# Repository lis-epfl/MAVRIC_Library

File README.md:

# MAV'RIC Library
Open source library for MAV'RIC autopilots

For information about the installation and usage, have a look at the [Online Documentation](http://lis-epfl.github.io/MAVRIC_Library/) and the [Doxygen Documentation](http://lis-epfl.github.io/MAVRIC_Library/doxygen/classes.html)

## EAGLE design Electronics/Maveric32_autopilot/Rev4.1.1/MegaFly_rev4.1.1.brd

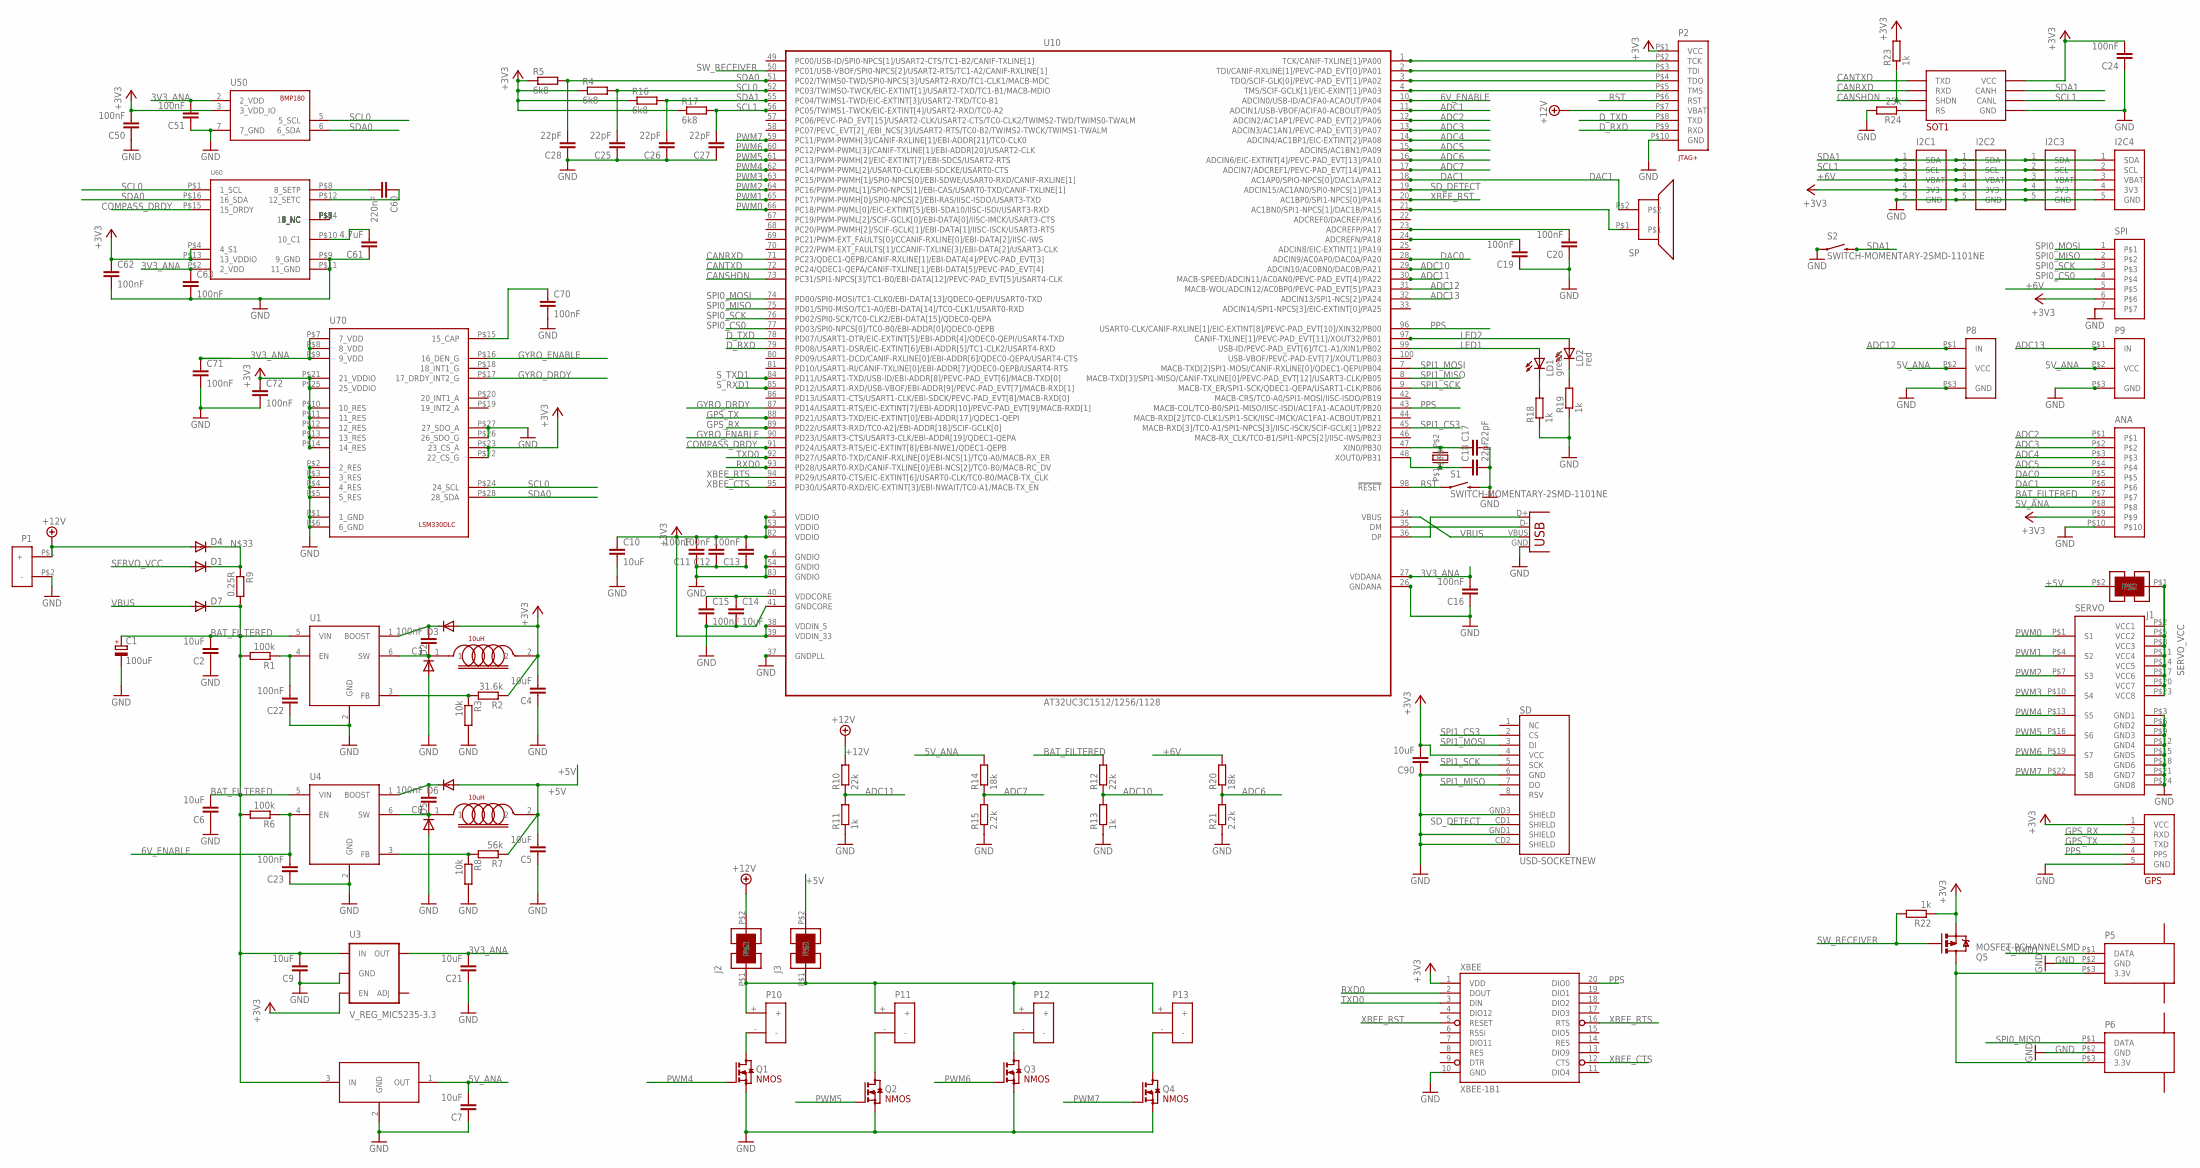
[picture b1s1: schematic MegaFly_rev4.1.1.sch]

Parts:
ANA: MOLEX_CONNECTOR_10PINSMOLEX_PICOBLADE; MOLEX_CONNECTOR_10PINS
C1: 100uF; D/7343-31R
C2, C4, C5, C6, C7, C9, C10, C14, C21, C90: 10uF; C0805
C3, C8, C11, C12, C13, C15, C16, C19, C20, C22, C23, C24, C50, C51, C62, C63, C70, C71, C72: 100nF; C0603
C17, C18, C25, C26, C27, C28: 22pF; C0402
C60: 220nF; C0805
C61: 4.7uF; C0805
D1, D2, D3, D4, D5, D6, D7: DIODESOD; SOD-323
GPS: APM2.5_GPS_HEADERVERTICAL; MOLEX_CONNECTOR_5_PINS_VERTICAL
I2C1, I2C2, I2C3, I2C4: I2C_BUS_PICOVERTICAL; MOLEX_CONNECTOR_5_PINS_VERTICAL
J1, J2, J3: SOLDER_JUMPER_2WAY
L1, L2: 10uH; C1210
LD1: green; CHIPLED_0805
LD2: red; CHIPLED_0805
P1: POWER
P2: AVR32_JTAG+SERIALMOLEX_PICOBLADE; MOLEX_CONNECTOR_10PINS
P5, P6: SPEKTRUM_RECEIVER; JST_1.5MM_3WAY
P8, P9: SENSOR; SERVO_COMPACT
P10, P11, P12, P13: POWERSMALL_SMD; POWER_SMALL_SMD
Q1, Q2, Q3, Q4: N-CHANNEL_SOT23; SOT23
Q5: MOSFET-PCHANNELSMD; SOT23-3
R1, R6: 100k; R0603
R2: 31.6k; R0603
R3, R8: 10k; R0603
R4, R5, R16, R17: 6k8; R0603
R7: 56k; R0603
R9: 0.25R; R0805
R10, R12: 22k; R0603
R11, R13, R18, R19, R22, R23: 1k; R0603
R14, R20: 18k; R0603
R15, R21: 2.2k; R0603
R24: 25k; R0603
S1, S2: SWITCH-MOMENTARY-2SMD-1101NE; TACTILE-SWITCH-1101NE
SD: USD-SOCKETNEW; MICRO-SD-SOCKET-PP
SERVO: SERVOCONNECTOR_X8STANDARD; HEADER3X8
SOT1: MAX3051; SOT23-8L
SP: PIEZO_SPEAKERSMALLER; PIEZO_CMT_1203-SMT-REDUCED_FOOTPRINT
SPI: MOLEX_CONNECTOR_7PINS
U1, U4: LM2734; SOT23-6
U2: MC78L05; SOT89
U3: V_REG_MIC5235-3.3; SOT23-5
U10: AT32UC3C1512/1256/1128; TQFP100
U50: BMP180
U60: HMC5883L; LPCC16_0.5MM
U70: LSM330DLC
USB: USB-MICROB
X1: CRYSTAL:ABM_16MHz; SMD_CRYSTAL_ABM
XBEE: XBEE-1B1; XBEE-1

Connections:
3V3_ANA: C16.2, C21.2, C51.2, C63.1, C71.1, U3.5 (OUT), U10.27 (VDDANA), U50.2 (2_VDD), U60.P$2 (2_VDD), U70.P$7 (7_VDD), U70.P$8 (8_VDD), U70.P$9 (9_VDD)
5V_ANA: ANA.P$8, C7.2, P8.P$2 (VCC), P9.P$2 (VCC), R14.2, U2.1 (OUT)
6V_ENABLE: C23.2, R6.1, U4.4 (EN), U10.10 (ADCIN0/USB-ID/ACIFA0-ACAOUT/PA04)
+3V3: ANA.P$9, C4.2, C10.1, C11.2, C12.2, C13.2, C24.2, C50.2, C62.1, C72.1, C90.2, D3.2 (A), GPS.1 (VCC), I2C1.4 (3V3), I2C2.4 (3V3), I2C3.4 (3V3), I2C4.4 (3V3), L1.2, P2.P$1 (VCC), Q5.2 (S), R2.1, R4.1, R5.1, R16.1, R17.1, R22.1, R23.2, SD.4 (VCC), SOT1.P$3 (VCC), SPI.6, U3.3 (EN), U10.5 (VDDIO), U10.38 (VDDIN_5), U10.39 (VDDIN_33), U10.53 (VDDIO), U10.82 (VDDIO), U50.3 (3_VDD_IO), U60.P$4 (4_S1), U60.P$13 (13_VDDIO), U70.P$10 (10_RES), U70.P$11 (11_RES), U70.P$12 (12_RES), U70.P$13 (13_RES), U70.P$14 (14_RES), U70.P$21 (21_VDDIO), U70.P$22 (22_CS_G), U70.P$23 (23_CS_A), U70.P$25 (25_VDDIO), XBEE.1 (VDD)
+12V: D4.2 (A), J2.P$2, P1.P$1 (+), P2.P$7 (VBAT), R10.2
ADC1: U10.11 (ADCIN1/USB-VBOF/ACIFA0-ACBOUT/PA05)
ADC2: ANA.P$1, U10.12 (ADCIN2/AC1AP1/PEVC-PAD_EVT[2]/PA06)
ADC3: ANA.P$2, U10.13 (ADCIN3/AC1AN1/PEVC-PAD_EVT[3]/PA07)
ADC4: ANA.P$3, U10.14 (ADCIN4/AC1BP1/EIC-EXTINT[2]/PA08)
ADC5: ANA.P$4, U10.15 (ADCIN5/AC1BN1/PA09)
ADC6: R20.1, R21.2, U10.16 (ADCIN6/EIC-EXTINT[4]/PEVC-PAD_EVT[13]/P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)
ADC7: R14.1, R15.2, U10.17 (ADCIN7/ADCREF1/PEVC-PAD_EVT[14]/PA11)
ADC10: R12.1, R13.2, U10.29 (ADCIN10/AC0BN0/DAC0B/PA21)
ADC11: R10.1, R11.2, U10.30 (MACB-SPEED/ADCIN11/AC0AN0/PEVC-PAD_EVT[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)
ADC12: P8.P$1 (IN), U10.31 (MACB-WOL/ADCIN12/AC0BP0/PEVC-PAD_EVT[5]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)
ADC13: P9.P$1 (IN), U10.32 (ADCIN13/SPI1-NCS[2]/PA24)
BAT_FILTERED: ANA.P$7, C1.+, C2.2, C6.2, C9.2, D7.1 (C), R1.2, R6.2, R9.2, R12.2, U1.5 (VIN), U2.3 (IN), U3.1 (IN), U4.5 (VIN)
CANRXD: SOT1.P$4 (RXD), U10.71 (PC23/QDEC1-QEPB/CANIF-RXLINE[1]/EBI-DAT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)
CANSHDN: R23.1, SOT1.P$5 (SHDN), U10.73 (PC31/SPI1-NPCS[3]/TC1-B0/EBI-DATA[12]/P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)
CANTXD: SOT1.P$1 (TXD), U10.72 (PC24/QDEC1-QEPA/CANIF-TXLINE[1]/EBI-DAT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)
COMPASS_DRDY: U10.91 (PD24/USART3-RTS/EIC-EXTINT[8]/EBI-NWE1/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), U60.P$15 (15_DRDY)
DAC0: ANA.P$5, U10.28 (ADCIN9/AC0AP0/DAC0A/PA20)
DAC1: ANA.P$6, SP.P$2, U10.18 (AC1AP0/SPIO-NPCS[0]/DAC1A/PA12)
D_RXD: P2.P$9 (RXD), U10.79 (PD08/USART1-DSR/EIC-EXTINT[6]/EBI-ADDR[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)
D_TXD: P2.P$8 (TXD), U10.78 (PD07/USART1-DTR/EIC-EXTINT[5]/EBI-ADDR[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)
GND: ANA.P$10, C1.-, C2.1, C4.1, C5.1, C6.1, C7.1, C9.1, C10.2, C11.1, C12.1, C13.1, C14.2, C15.2, C16.1, C17.2, C18.2, C19.1, C20.1, C21.1, C22.1, C23.1, C24.1, C25.1, C26.1, C27.1, C28.1, C50.1, C51.1, C61.1, C62.2, C63.2, C70.2, C71.2, C72.2, C90.1, D2.2 (A), D5.2 (A), GPS.5 (GND), I2C1.5 (GND), I2C2.5 (GND), I2C3.5 (GND), I2C4.5 (GND), P1.P$2 (-), P2.P$10 (GND), P5.P$2 (GND), P6.P$2 (GND), P8.P$3 (GND), P9.P$3 (GND), Q1.2 (S), Q2.2 (S), Q3.2 (S), Q4.2 (S), R3.2, R8.2, R11.1, R13.1, R15.1, R18.1, R19.1, R21.1, R24.2, S1.P$2 (2), S2.P$1 (1), SD.6 (GND), SD.CD2 (SHIELD), SD.GND1 (SHIELD), SD.GND3 (SHIELD), SERVO.P$3 (GND1), SERVO.P$6 (GND2), SERVO.P$9 (GND3), SERVO.P$12 (GND4), SERVO.P$15 (GND5), SERVO.P$18 (GND6), SERVO.P$21 (GND7), SERVO.P$24 (GND8), SOT1.P$2 (GND), SPI.7, U1.2 (GND), U2.2 (GND), U3.2 (GND), U4.2 (GND), U10.6 (GNDIO), U10.26 (GNDANA), U10.37 (GNDPLL), U10.41 (GNDCORE), U10.54 (GNDIO), U10.83 (GNDIO), U50.7 (7_GND), U60.P$9 (9_GND), U60.P$11 (11_GND), U70.P$1 (1_GND), U70.P$2 (2_RES), U70.P$3 (3_RES), U70.P$4 (4_RES), U70.P$5 (5_RES), U70.P$6 (6_GND), U70.P$26 (26_SDO_G), U70.P$27 (27_SDO_A), USB.GND, XBEE.10 (GND)
GPS_RX: GPS.2 (RXD), U10.89 (PD22/USART3-RXD/TC0-A2]/EBI-ADDR[18]/SC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)
GPS_TX: GPS.3 (TXD), U10.88 (PD21/USART3-TXD/EIC-EXTINT[0]/EBI-ADDR[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)
GYRO_DRDY: U10.87 (PD14/USART1-RTS/EIC-EXTINT[7]/EBI-ADDR[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), U70.P$17 (17_DRDY_INT2_G)
GYRO_ENABLE: U10.90 (PD23/USART3-CTS/USART3-CLK/EBI-ADDR[19]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), U70.P$16 (16_DEN_G)
LED1: LD1.A, U10.99 (USB-ID/PEVC-PAD_EVT[6]/TC1-A1/XIN1/PB02)
LED2: LD2.A, U10.97 (CANIF-TXLINE[1]/PEVC-PAD_EVT[11]/XOUT32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)
unnamed: P2.P$5 (TMS), U10.4 (TMS/SCIF-GCLK[1]/EIC-EXINT[1]/PA03)
unnamed: P2.P$4 (TDO), U10.3 (TDO/SCIF-GLK[0]/PEVC-PAD_EVT[1]/PA02)
unnamed: C18.1, U10.48 (XOUT0/PB31), X1.P$1
unnamed: C17.1, U10.47 (XIN0/PB30), X1.P$2
unnamed: LD1.C, R18.2
unnamed: C22.2, R1.1, U1.4 (EN)
unnamed: LD2.C, R19.2
unnamed: C3.1, D2.1 (C), L1.1, U1.6 (SW)
unnamed: R2.2, R3.1, U1.3 (FB)
unnamed: C3.2, D3.1 (C), U1.1 (BOOST)
unnamed: SP.P$1, U10.21 (AC1BN0/SPI1-NPCS[1]/DAC1B/PA15)
unnamed: C61.2, U60.P$10 (10_C1)
unnamed: C60.2, U60.P$8 (8_SETP)
unnamed: C60.1, U60.P$12 (12_SETC)
unnamed: C70.1, U70.P$15 (15_CAP)
unnamed: J2.P$1, J3.P$1, P10.+, P11.+, P12.+, P13.+
unnamed: P2.P$3 (TDI), U10.2 (TDI/CANIF-RXLINE[1]/PEVC-PAD_EVT[0]/PA01)
unnamed: C8.1, D5.1 (C), L2.1, U4.6 (SW)
unnamed: C14.1, C15.1, U10.40 (VDDCORE)
unnamed: R7.2, R8.1, U4.3 (FB)
unnamed: C8.2, D6.1 (C), U4.1 (BOOST)
unnamed: P10.-, Q1.3 (D)
unnamed: P11.-, Q2.3 (D)
unnamed: P12.-, Q3.3 (D)
unnamed: P13.-, Q4.3 (D)
unnamed: U10.36 (DP), USB.D+
unnamed: P2.P$2 (TCK), U10.1 (TCK/CANIF-TXLINE[1]/PA00)
unnamed: U10.35 (DM), USB.D-
unnamed: C19.2, U10.24 (ADCREFN/PA18)
unnamed: C20.2, U10.23 (ADCREFP/PA17)
unnamed: D1.1 (C), D4.1 (C), R9.1
unnamed: P5.P$3 (3.3V), P6.P$3 (3.3V), Q5.3 (D)
unnamed: R24.1, SOT1.P$8 (RS)
PPS: GPS.4 (PPS), U10.43 (MACB-COL/TC0-B0/SPI1-MISO/IISC-ISDI/AC1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), U10.96 (USART0-CLK/CANIF-RXLINE[1]/EIC-EXTINT[8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), XBEE.20 (DIO0)
PWM0: SERVO.P$1 (S1), U10.66 (PC18/PWM-PWML[0]/EIC-EXTINT[5]/EBI-SDA1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)
PWM1: SERVO.P$4 (S2), U10.65 (PC17/PWM-PWMH[0]/SPI0-NPCS[2]/EBI-RAS/I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)
PWM2: SERVO.P$7 (S3), U10.64 (PC16/PWM-PWML[1]/SPI0-NPCS[1]/EBI-CAS/U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)
PWM3: SERVO.P$10 (S4), U10.63 (PC15/PWM-PWMH[1]/SPI0-NPCS[0]/EBI-SDWE/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)
PWM4: Q1.1 (G), SERVO.P$13 (S5), U10.62 (PC14/PWM-PWML[2]/USART0-CLK/EBI-SDCKE/U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)
PWM5: Q2.1 (G), SERVO.P$16 (S6), U10.61 (PC13/PWM-PWMH[2]/EIC-EXTINT[7]/EBI-SDCS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)
PWM6: Q3.1 (G), SERVO.P$19 (S7), U10.60 (PC12/PWM-PWML[3]/CANIF-TXLINE[1]/EBI-AD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)
PWM7: Q4.1 (G), SERVO.P$22 (S8), U10.59 (PC11/PWM-PWMH[3]/CANIF-RXLINE[1]/EBI-AD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)
RST: P2.P$6 (RST), S1.P$1 (1), U10.98 (!RESET)
RXD0: U10.93 (PD28/USART0-RXD/CANIF-TXLINE[0]/EBI-NCS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), XBEE.2 (DOUT)
SCL0: C25.2, R4.2, U10.52 (PC03/TWIMSO-TWCK/EIC-EXTINT[1]/USART2-T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), U50.5 (5_SCL), U60.P$1 (1_SCL), U70.P$24 (24_SCL)
SCL1: C27.2, I2C1.2 (SCL), I2C2.2 (SCL), I2C3.2 (SCL), I2C4.2 (SCL), R17.2, SOT1.P$6 (CANL), U10.56 (PC05/TWIMS1-TWCK/EIC-EXTINT[4]/USART2-R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)
SDA0: C28.2, R5.2, U10.51 (PC02/TWIMS0-TWD/SPI0-NPCS[3]/USART2-RXD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), U50.6 (6_SDA), U60.P$16 (16_SDA), U70.P$28 (28_SDA)
SDA1: C26.2, I2C1.1 (SDA), I2C2.1 (SDA), I2C3.1 (SDA), I2C4.1 (SDA), R16.2, S2.P$2 (2), SOT1.P$7 (CANH), U10.55 (PC04/TWIMS1-TWD/EIC-EXTINT[3]/USART2-TX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)
SD_DETECT: SD.CD1 (SHIELD), U10.19 (ADCIN15/AC1AN0/SPI0-NPCS[1]/PA13)
SERVO_VCC: D1.2 (A), J1.P$1, SERVO.P$2 (VCC1), SERVO.P$5 (VCC2), SERVO.P$8 (VCC3), SERVO.P$11 (VCC4), SERVO.P$14 (VCC5), SERVO.P$17 (VCC6), SERVO.P$20 (VCC7), SERVO.P$23 (VCC8)
SPI0_CS0: SPI.4, U10.77 (PD03/SPI0-NPCS[0]/TC0-B0/EBI-ADDR[0]/QD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)
SPI0_MISO: P6.P$1 (DATA), SPI.2, U10.75 (PD01/SPI0-MISO/TC1-A0/EBI-DATA[14]/TC0-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)
SPI0_MOSI: SPI.1, U10.74 (PD00/SPI0-MOSI/TC1-CLK0/EBI-DATA[13]/QD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)
SPI0_SCK: SPI.3, U10.76 (PD02/SPI0-SCK/TC0-CLK2/EBI-DATA[15]/QDE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)
SPI1_CS3: SD.2 (CS), U10.45 (MACB-RXD[3]/TC0-A1/SPI1-NPCS[3]/IISC-IS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)
SPI1_MISO: SD.7 (DO), U10.8 (MACB-TXD[3]/SPI1-MISO/CANIF-TXLINE[0]/P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)
SPI1_MOSI: SD.3 (DI), U10.7 (MACB-TXD[2]SPI1-MOSI/CANIF-RXLINE[0]/QD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)
SPI1_SCK: SD.5 (SCK), U10.9 (MACB-TX_ER/SPI1-SCK/QDEC1-QEPA/USART1-C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)
SW_RECEIVER: Q5.1 (G), R22.2, U10.50 (PC01/USB-VBOF/SPI0-NPCS[2]/USART2-RTS/T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)
S_RXD1: P5.P$1 (DATA), U10.85 (PD12/USART1-RXD/USB-VBOF/EBI-ADDR[9]/PE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)
S_TXD1: U10.84 (PD11/USART1-TXD/USB-ID/EBI-ADDR[8]/PEVC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)
TXD0: U10.92 (PD27/USART0-TXD/CANIF-RXLINE[0]/EBI-NCS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), XBEE.3 (DIN)
VBUS: D7.2 (A), U10.34 (VBUS), USB.VBUS
XBEE_CTS: U10.95 (PD30/USART0-RXD/EIC-EXTINT[3]/EBI-NWAIT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), XBEE.12 (CTS)
XBEE_RST: U10.20 (AC1BP0/SPI1-NPCS[0]/PA14), XBEE.5 (RESET)
XBEE_RTS: U10.94 (PD29/USART0-CTS/EIC-EXTINT[6]/USART0-CL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), XBEE.16 (RTS)

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
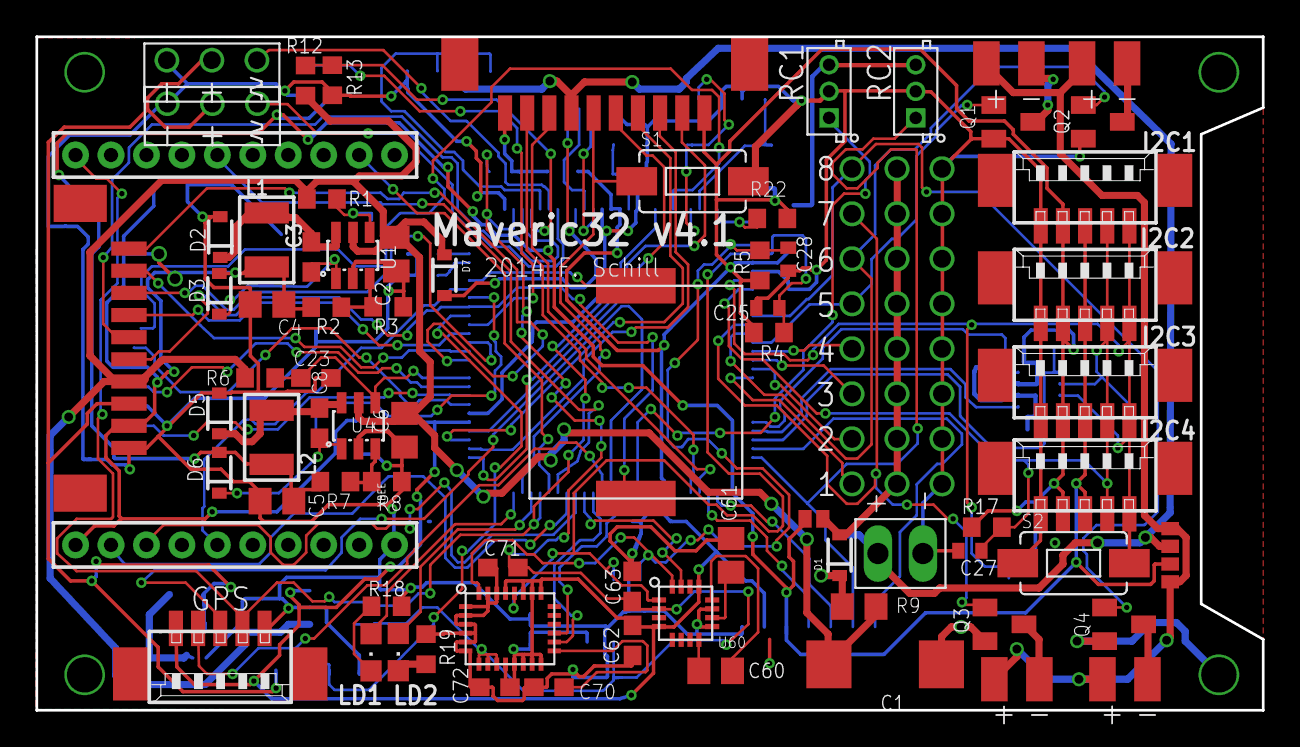
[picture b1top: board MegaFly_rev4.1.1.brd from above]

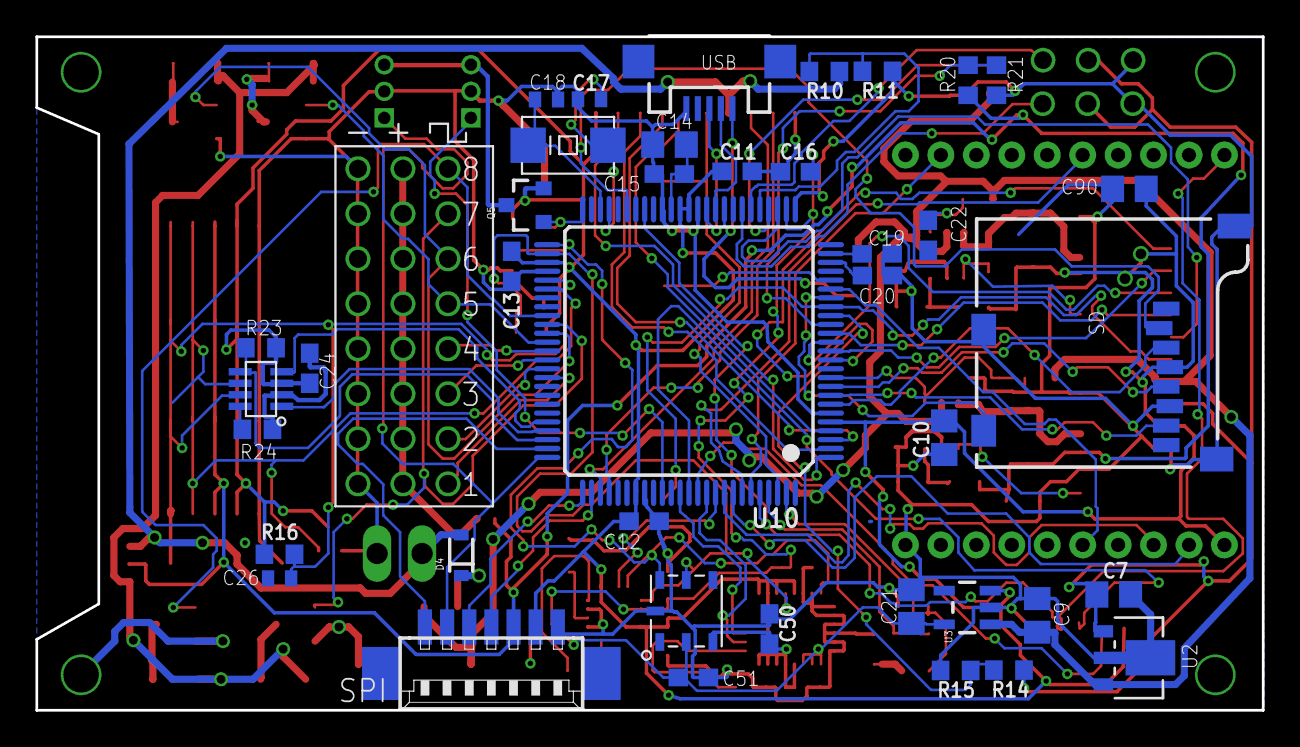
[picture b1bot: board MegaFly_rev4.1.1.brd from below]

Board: 2 copper layers, 69.2 x 38.0 mm, 115 parts (41 on the bottom side), 97 nets.

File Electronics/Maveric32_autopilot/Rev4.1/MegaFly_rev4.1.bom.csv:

Partlist exported from /home/felix/Scinamics/Designs/Avionics/MegaFly/MegaFly_rev4.1.sch at 2/6/14 3:21 PM,,,,,,,,,,
Qty,Parts,Device,Value,Description,Place(y/n),Distributor,Ordercode,Unit Price,Pricebreak,Total Price
40,ANA,MOLEX_CONNECTOR_10PINSHIROSE_DF13,MOLEX_CONNECTOR_10PINSHIROSE_DF13,"Molex Connector : PicoBlade 1.25 mm pitch, 10 pins, Vertical SMD",YES,Digikey,H3375-ND,0.638,10,25.52
40,C1,CPOL-EUD/7343-31R,100uF,"POLARIZED CAPACITOR, European symbol",YES,Digikey,718-1744-1-ND,1.002,10,40.08
240,"C17, C18, C25, C26, C27, C28",C-EUC0402,22pF,"CAPACITOR, European symbol",YES,,,,1,0
400,"C2, C4, C5, C6, C7, C9, C10, C14, C21, C90",C-EUC0805,10uF,"CAPACITOR, European symbol",YES,,,,1,0
760,"C3, C8, C11, C12, C13, C15, C16, C19, C20, C22, C23, C24, C50, C51, C62, C63, C70, C71, C72",C-EUC0603,100nF,"CAPACITOR, European symbol",YES,,,,1,0
40,C60,C-EUC0805,220nF,"CAPACITOR, European symbol",YES,,,,1,0
40,C61,C-EUC0805,4.7uF,"CAPACITOR, European symbol",YES,,,,1,0
280,"D1, D2, D3, D4, D5, D6, D7",DIODESOD,,Diode,YES,Digikey,568-4128-1-ND,0.1904,100,53.312
50,GPS,APM2.5_GPS_HEADERHIROSE_DF13_VERTICAL,APM2.5_GPS_HEADERHIROSE_DF13_VERTICAL,,YES,Digikey,H3396-ND,0.3676,50,18.38
160,"I2C1, I2C2, I2C3, I2C4",I2C_BUS_PICOHIROSE_DF13_VERTICAL,I2C_BUS_PICOHIROSE_DF13_VERTICAL,,YES,Digikey,H2222-ND,0.3524,100,56.384
0,"J1, J2, J3",SOLDER_JUMPER_2WAY,SOLDER_JUMPER_2WAY,,NO,,,,1,0
80,"L1, L2",INDUCTOR1210,10uH,,YES,Digikey,445-4847-1-ND,0.262,50,20.96
40,LD1,LEDCHIPLED_0805_GREEN,green,LED,YES,Digikey,754-1057-1-ND,0.1508,25,6.032
40,LD2,LEDCHIPLED_0805_RED,red,LED,YES,Digikey,754-1132-1-ND,0.09,25,3.6
0,P1,POWER,POWER,,NO,,,,1,0
0,"P10, P11, P12, P13",POWERSMALL_SMD,POWERSMALL_SMD,,NO,,,,1,0
40,P2,AVR32_JTAG+SERIALHIROSE_DF13,AVR32_JTAG+SERIALHIROSE_DF13,"Unified compact debug port with JTAG, 7-12V power supply (VBAT) and serial port.",YES,Digikey,H3375-ND,0.638,10,25.52
0,"P5, P6",SPEKTRUM_RECEIVER,SPEKTRUM_RECEIVER,,NO,,,,1,0
0,"P8, P9",SENSOR,SENSOR,,NO,,,,1,0
160,"Q1, Q2, Q3, Q4",N-CHANNEL_SOT23,N-CHANNEL_SOT23,N-CHANNEL MOS FET,YES,Digikey,IRLML6244TRPBFCT-ND,0.1517,100,24.272
40,Q5,MOSFET-PCHANNELSMD,MOSFET-PCHANNELSMD,,YES,Digikey,SSM3J328RLF(TCT-ND,0.24,25,9.6
80,"R1, R6",R-EU_R0603,100k,"RESISTOR, European symbol",NO,,,,1,0
80,"R10, R12",R-EU_R0603,22k,"RESISTOR, European symbol",YES,,,,1,0
240,"R11, R13, R18, R19, R22, R23",R-EU_R0603,1k,"RESISTOR, European symbol",YES,,,,1,0
80,"R14, R20",R-EU_R0603,18k,"RESISTOR, European symbol",YES,,,,1,0
80,"R15, R21",R-EU_R0603,2.2k,"RESISTOR, European symbol",YES,,,,1,0
40,R2,R-EU_R0603,31.6k,"RESISTOR, European symbol",YES,,,,1,0
40,R24,R-EU_R0603,25k,"RESISTOR, European symbol",YES,,,,1,0
80,"R3, R8",R-EU_R0603,10k,"RESISTOR, European symbol",YES,,,,1,0
160,"R4, R5, R16, R17",R-EU_R0603,6k8,"RESISTOR, European symbol",YES,,,,1,0
40,R7,R-EU_R0603,68k,"RESISTOR, European symbol",YES,,,,1,0
40,R9,R-EU_R0805,0.25R,"RESISTOR, European symbol",YES,,,,1,0
40,S1,SWITCH-MOMENTARY-2SMD-1101NE,SWITCH-MOMENTARY-2SMD-1101NE,,YES,Digikey,450-1140-ND,0.1364,25,5.456
40,SD,USD-SOCKETNEW,USD-SOCKETNEW,microSD Socket,YES,Mouser,517-2908-05WB-MG,1.74,25,69.6
0,SERVO,SERVOCONNECTOR_X8STANDARD,SERVOCONNECTOR_X8STANDARD,,NO,,,,1,0
40,SOT1,MAX3051,MAX3051,,YES,Mouser,700-MAX3051EKAT,2.02,25,80.8
40,SP,PIEZO_SPEAKERSMALLER,PIEZO_SPEAKERSMALLER,,YES,Digikey,102-2197-1-ND,1.641,10,65.64
40,SPI,MOLEX_CONNECTOR_7PINSHIROSE_DF13,MOLEX_CONNECTOR_7PINSHIROSE_DF13,"Molex Picoblade connector, 7 pins SMD",YES,Digikey,H2224-ND,0.556,10,22.24
100,"U1, U4",LM2734,LM2734,,YES,Digikey,LM2734ZMK/NOPBCT-ND,1.3226,100,132.26
40,U10,AT32UC3C1512/1256/1128,AT32UC3C1512/1256/1128,AT32UC3C1512/1256/1128,YES,Digikey,AT32UC3C1512C-AUT-ND,9.0568,25,362.272
40,U2,LDO_3PINSOT89_MC78LXX,MC78L05,,YES,Digikey,MC78L05ACHXCT-ND,0.274,25,10.96
40,U3,V_REG_MIC5235,V_REG_MIC5235-3.3,,YES,Digikey,576-2784-1-ND,0.7084,25,28.336
40,U50,BMP180,BMP180,,YES,Rutronik,BMP180,3.45,1,138
40,U60,HMC5883L,HMC5883L,,YES,Digikey,342-1082-1-ND,1.638,25,65.52
40,U70,LSM330DLC,LSM330DLC,,YES,Mouser,511-LSM330DLC,4.3,25,172
40,USB,USB-MICROB,USB-MICROB,USB Connectors,YES,Digikey,609-4613-1-ND,0.2992,25,11.968
40,X1,CRYSTAL,CRYSTAL:ABM_16MHz,,YES,Digikey,535-9840-1-ND,0.683,10,27.32
0,XBEE,XBEE-1B1,XBEE-1B1,,NO,,,,1,0
,,,,,,,Avg. per board:,36.9008,Overall total:,1476.032

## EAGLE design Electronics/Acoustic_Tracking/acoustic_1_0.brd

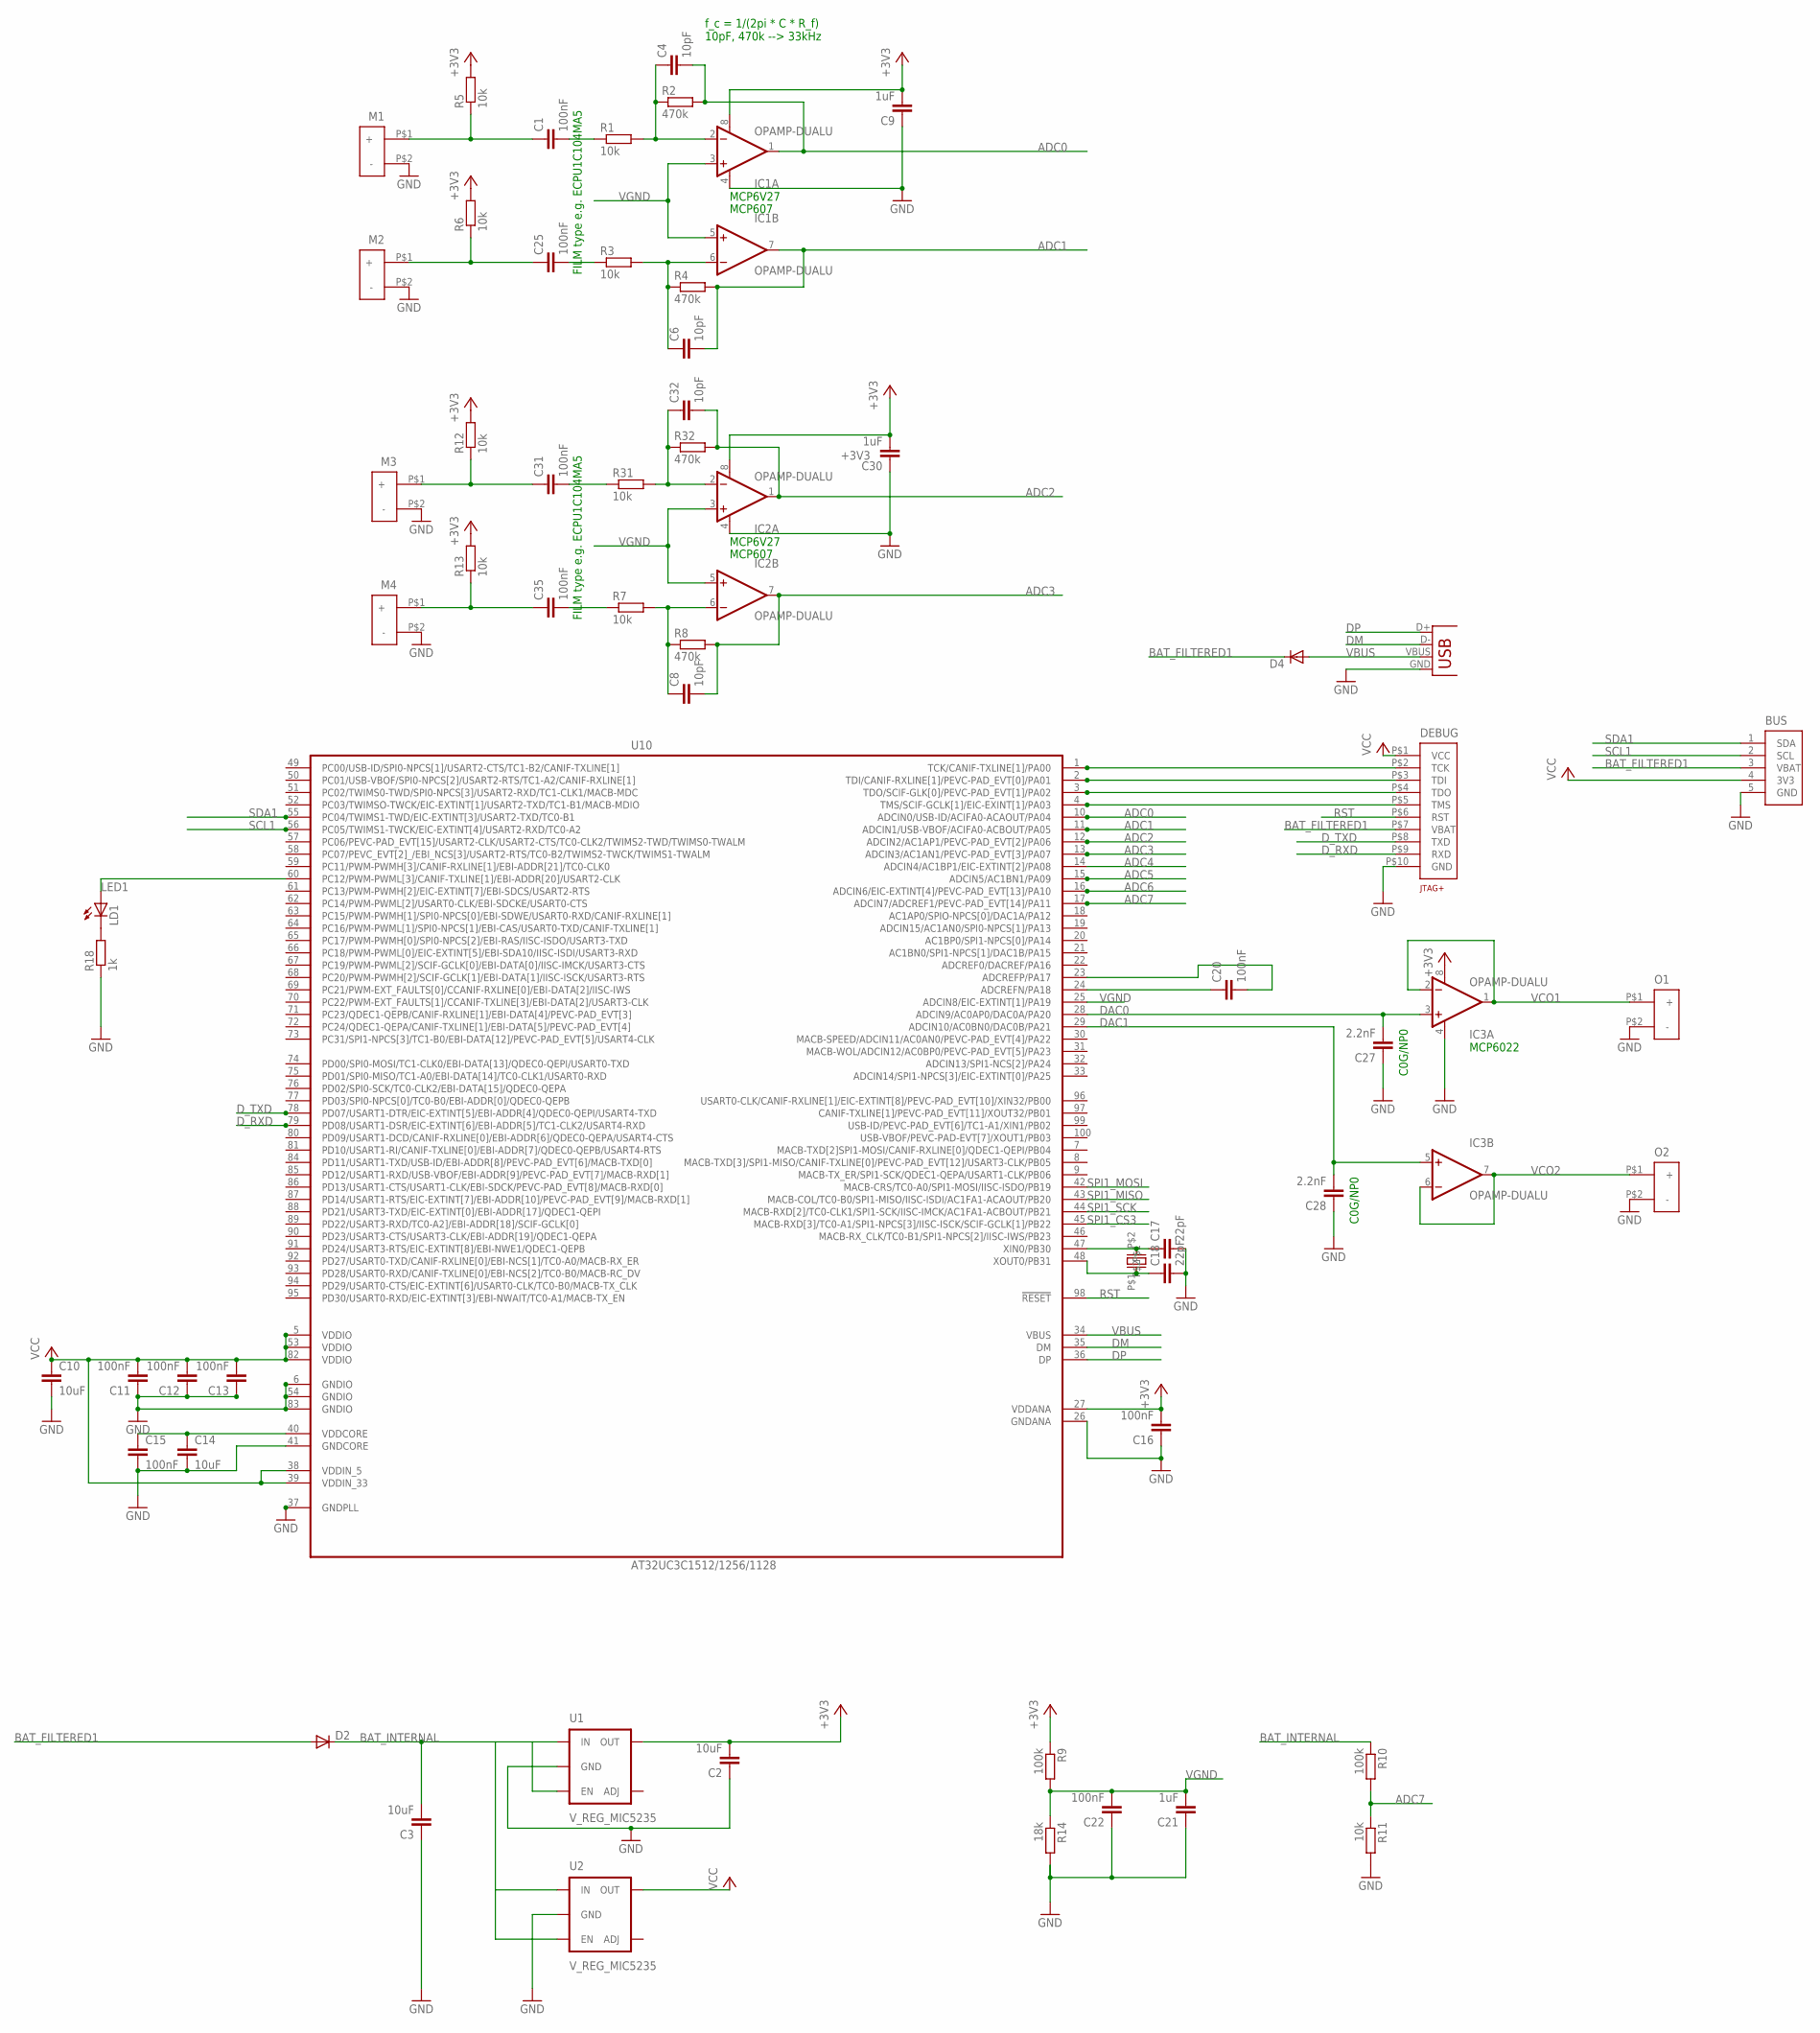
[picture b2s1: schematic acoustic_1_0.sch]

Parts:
BUS: I2C_BUS_PICOVERTICAL; MOLEX_CONNECTOR_5_PINS_VERTICAL
C1, C25, C31, C35: 100nF; C0805
C2, C3, C10, C14: 10uF; C0805
C4, C6, C8, C32: 10pF; C0603
C9, C21, C30: 1uF; C0805
C11, C12, C13, C15, C16, C20, C22: 100nF; C0603
C17, C18: 22pF; C0402
C27, C28: 2.2nF; C0805
D2, D4: DIODESOD; SOD-323
DEBUG: AVR32_JTAG+SERIALHIROSE_DF13; MOLEX_CONNECTOR_10PINS
IC1, IC2, IC3: OPAMP-DUALU; SO08
LD1: LEDCHIPLED_0805; CHIPLED_0805
M1, M2, M3, M4: POWER
O1, O2: POWER
R1, R3, R5, R6, R7, R11, R12, R13, R31: 10k; R0603
R2, R4, R8, R32: 470k; R0603
R9, R10: 100k; R0603
R14: 18k; R0603
R18: 1k; R0603
U1, U2: V_REG_MIC5235; SOT23-5
U10: AT32UC3C1512/1256/1128; TQFP100
U$8: CRYSTAL; SMD_CRYSTAL_ABM
X1: USB-MICROB

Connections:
+3V3: C2.2, C9.2, C16.2, C30.2, IC1.8 (V+), IC2.8 (V+), IC3.8 (V+), R5.2, R6.2, R9.1, R12.2, R13.2, U1.5 (OUT), U10.27 (VDDANA)
ADC0: C4.2, IC1.1 (OUT), R2.2, U10.10 (ADCIN0/USB-ID/ACIFA0-ACAOUT/PA04)
ADC1: C6.2, IC1.7 (OUT), R4.2, U10.11 (ADCIN1/USB-VBOF/ACIFA0-ACBOUT/PA05)
ADC2: C32.2, IC2.1 (OUT), R32.2, U10.12 (ADCIN2/AC1AP1/PEVC-PAD_EVT[2]/PA06)
ADC3: C8.2, IC2.7 (OUT), R8.2, U10.13 (ADCIN3/AC1AN1/PEVC-PAD_EVT[3]/PA07)
ADC4: U10.14 (ADCIN4/AC1BP1/EIC-EXTINT[2]/PA08)
ADC5: U10.15 (ADCIN5/AC1BN1/PA09)
ADC6: U10.16 (ADCIN6/EIC-EXTINT[4]/PEVC-PAD_EVT[13]/P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)
ADC7: R10.2, R11.1, U10.17 (ADCIN7/ADCREF1/PEVC-PAD_EVT[14]/PA11)
BAT_FILTERED1: BUS.3 (VBAT), D2.2 (A), D4.1 (C), DEBUG.P$7 (VBAT)
BAT_INTERNAL: C3.2, D2.1 (C), R10.1, U1.1 (IN), U1.3 (EN), U2.1 (IN), U2.3 (EN)
DAC0: C27.2, IC3.3 (+IN), U10.28 (ADCIN9/AC0AP0/DAC0A/PA20)
DAC1: C28.2, IC3.5 (+IN), U10.29 (ADCIN10/AC0BN0/DAC0B/PA21)
DM: U10.35 (DM), X1.D-
DP: U10.36 (DP), X1.D+
D_RXD: DEBUG.P$9 (RXD), U10.79 (PD08/USART1-DSR/EIC-EXTINT[6]/EBI-ADDR[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)
D_TXD: DEBUG.P$8 (TXD), U10.78 (PD07/USART1-DTR/EIC-EXTINT[5]/EBI-ADDR[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)
GND: BUS.5 (GND), C2.1, C3.1, C9.1, C10.2, C11.1, C12.1, C13.1, C14.2, C15.2, C16.1, C17.2, C18.2, C21.1, C22.1, C27.1, C28.1, C30.1, DEBUG.P$10 (GND), IC1.4 (V-), IC2.4 (V-), IC3.4 (V-), M1.P$2 (-), M2.P$2 (-), M3.P$2 (-), M4.P$2 (-), O1.P$2 (-), O2.P$2 (-), R11.2, R14.2, R18.1, U1.2 (GND), U2.2 (GND), U10.6 (GNDIO), U10.26 (GNDANA), U10.37 (GNDPLL), U10.41 (GNDCORE), U10.54 (GNDIO), U10.83 (GNDIO), X1.GND
LED1: LD1.A, U10.60 (PC12/PWM-PWML[3]/CANIF-TXLINE[1]/EBI-AD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)
unnamed: DEBUG.P$5 (TMS), U10.4 (TMS/SCIF-GCLK[1]/EIC-EXINT[1]/PA03)
unnamed: DEBUG.P$4 (TDO), U10.3 (TDO/SCIF-GLK[0]/PEVC-PAD_EVT[1]/PA02)
unnamed: C18.1, U10.48 (XOUT0/PB31), U$8.P$1
unnamed: C17.1, U10.47 (XIN0/PB30), U$8.P$2
unnamed: LD1.C, R18.2
unnamed: C25.2, R3.1
unnamed: C4.1, IC1.2 (-IN), R1.2, R2.1
unnamed: C20.2, U10.23 (ADCREFP/PA17)
unnamed: C6.1, IC1.6 (-IN), R3.2, R4.1
unnamed: C35.2, R7.1
unnamed: C1.2, R1.1
unnamed: C1.1, M1.P$1 (+), R5.1
unnamed: C25.1, M2.P$1 (+), R6.1
unnamed: C31.2, R31.1
unnamed: DEBUG.P$3 (TDI), U10.2 (TDI/CANIF-RXLINE[1]/PEVC-PAD_EVT[0]/PA01)
unnamed: C14.1, C15.1, U10.40 (VDDCORE)
unnamed: C32.1, IC2.2 (-IN), R31.2, R32.1
unnamed: C31.1, M3.P$1 (+), R12.1
unnamed: C35.1, M4.P$1 (+), R13.1
unnamed: C8.1, IC2.6 (-IN), R7.2, R8.1
unnamed: DEBUG.P$2 (TCK), U10.1 (TCK/CANIF-TXLINE[1]/PA00)
unnamed: C20.1, U10.24 (ADCREFN/PA18)
RST: DEBUG.P$6 (RST), U10.98 (!RESET)
SCL1: BUS.2 (SCL), U10.56 (PC05/TWIMS1-TWCK/EIC-EXTINT[4]/USART2-R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)
SDA1: BUS.1 (SDA), U10.55 (PC04/TWIMS1-TWD/EIC-EXTINT[3]/USART2-TX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)
SPI1_CS3: U10.45 (MACB-RXD[3]/TC0-A1/SPI1-NPCS[3]/IISC-IS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)
SPI1_MISO: U10.43 (MACB-COL/TC0-B0/SPI1-MISO/IISC-ISDI/AC1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)
SPI1_MOSI: U10.42 (MACB-CRS/TC0-A0/SPI1-MOSI/IISC-ISDO/PB19)
SPI1_SCK: U10.44 (MACB-RXD[2]/TC0-CLK1/SPI1-SCK/IISC-IMCK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)
VBUS: D4.2 (A), U10.34 (VBUS), X1.VBUS
VCC: BUS.4 (3V3), C10.1, C11.2, C12.2, C13.2, DEBUG.P$1 (VCC), U2.5 (OUT), U10.5 (VDDIO), U10.38 (VDDIN_5), U10.39 (VDDIN_33), U10.53 (VDDIO), U10.82 (VDDIO)
VCO1: IC3.1 (OUT), IC3.2 (-IN), O1.P$1 (+)
VCO2: IC3.6 (-IN), IC3.7 (OUT), O2.P$1 (+)
VGND: C21.2, C22.2, IC1.3 (+IN), IC1.5 (+IN), IC2.3 (+IN), IC2.5 (+IN), R9.2, R14.1, U10.25 (ADCIN8/EIC-EXTINT[1]/PA19)

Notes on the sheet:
f_c = 1/(2pi * C * R_f) 10pF, 470k --> 33kHz
MCP6V27
MCP607
MCP6022
FILM type e.g. ECPU1C104MA5
C0G/NP0

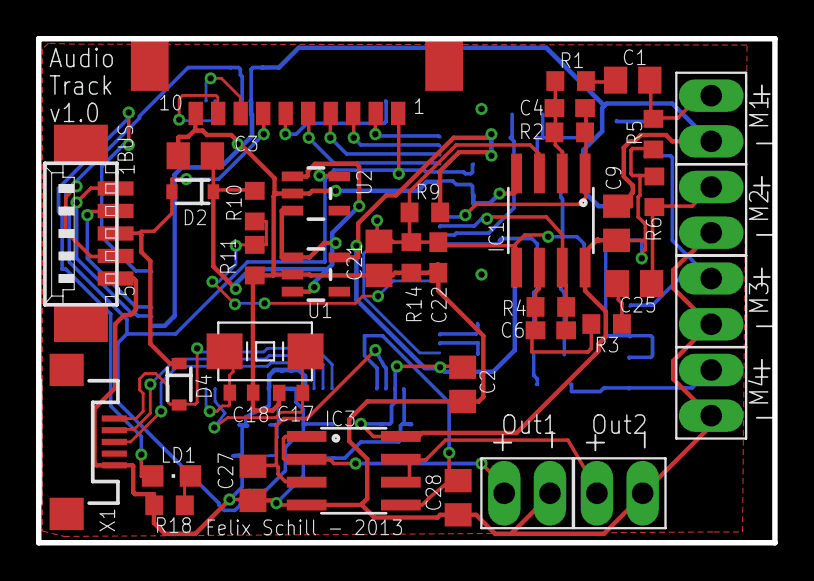
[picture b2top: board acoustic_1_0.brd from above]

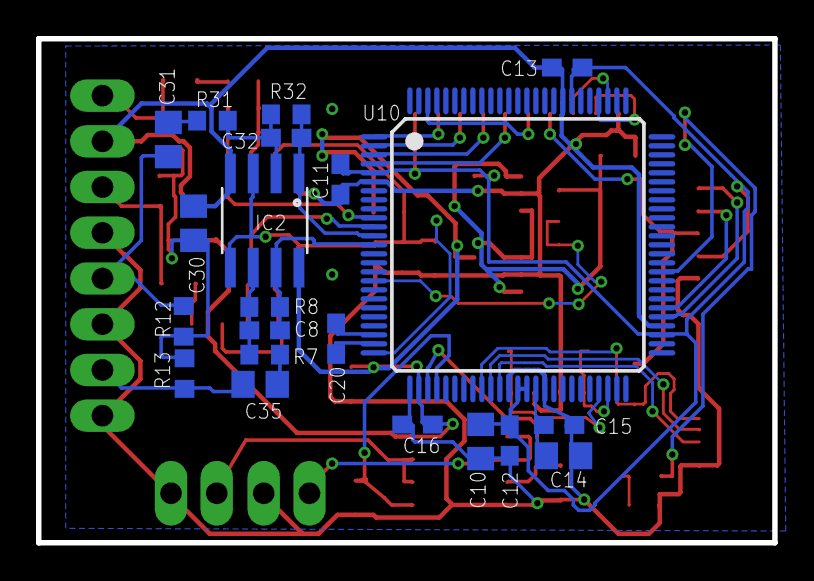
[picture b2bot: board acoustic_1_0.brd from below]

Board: 2 copper layers, 40.9 x 28.0 mm, 62 parts (21 on the bottom side), 46 nets.

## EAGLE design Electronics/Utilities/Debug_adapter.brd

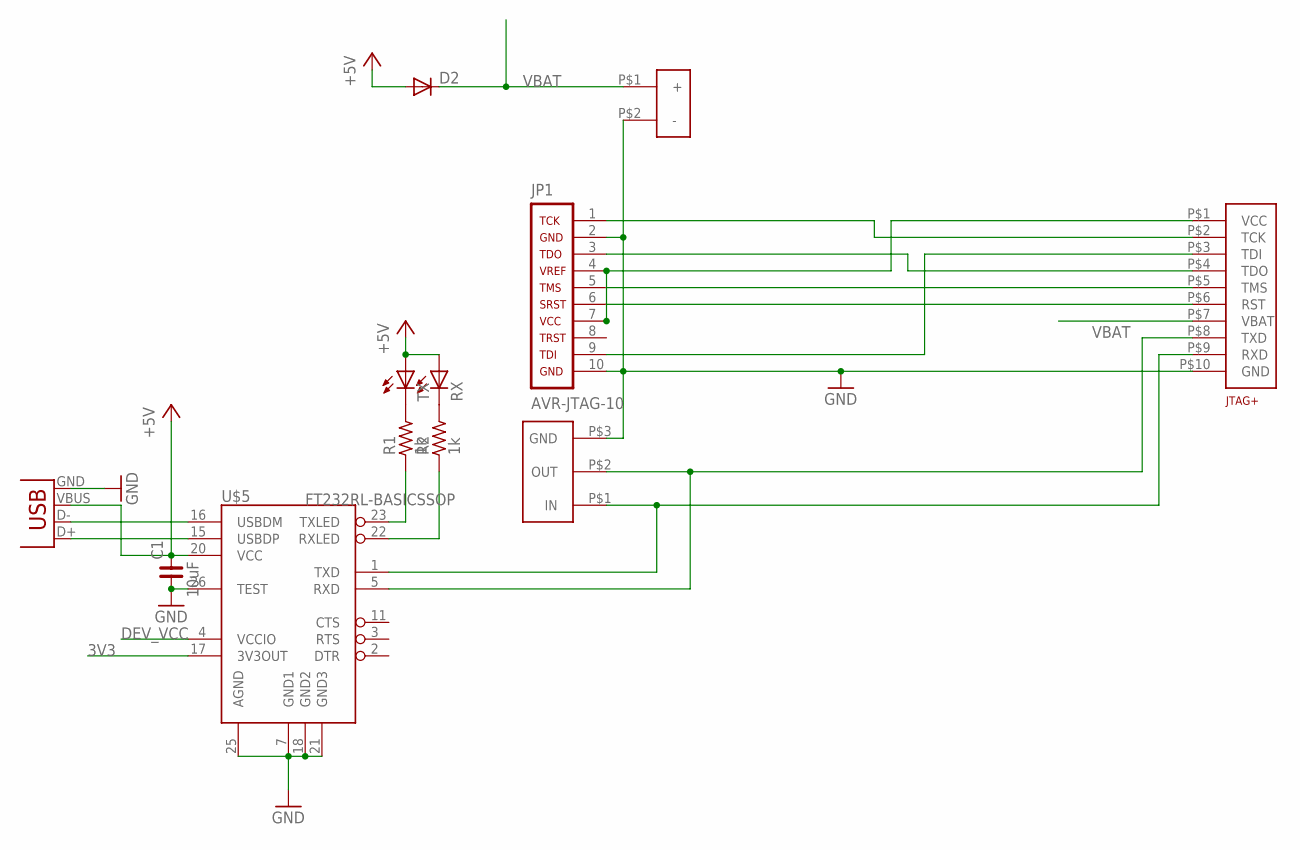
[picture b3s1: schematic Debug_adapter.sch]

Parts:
C1: 10uF; C0805
D2: DIODESOD; SOD-323
JP1: AVR-JTAG-10
R1, R2: 1k; R0805
RX: LEDCHIPLED_0805; CHIPLED_0805
TX: LEDCHIPLED_0805; CHIPLED_0805
U$1: AVR32_JTAG+SERIAL; MOLEX_CONNECTOR_10PINS
U$2: POWER
U$3: SERIAL; SERVO
U$5: FT232RL-BASICSSOP; SSOP28DB
X1: USBSMD; USB-MINIB

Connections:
3V3: U$5.17 (3V3OUT)
+5V: C1.2, D2.2 (A), RX.A, TX.A, U$5.20 (VCC), X1.VBUS
DEV_VCC: U$5.4 (VCCIO)
GND: C1.1, JP1.2, JP1.10, U$1.P$10 (GND), U$2.P$2 (-), U$3.P$3 (GND), U$5.7 (GND1), U$5.18 (GND2), U$5.21 (GND3), U$5.25 (AGND), U$5.26 (TEST), X1.GND
unnamed: JP1.1, U$1.P$2 (TCK)
unnamed: JP1.9, U$1.P$3 (TDI)
unnamed: JP1.3, U$1.P$4 (TDO)
unnamed: JP1.5, U$1.P$5 (TMS)
unnamed: JP1.6, U$1.P$6 (RST)
unnamed: JP1.4, JP1.7, U$1.P$1 (VCC)
unnamed: U$5.16 (USBDM), X1.D-
unnamed: U$5.15 (USBDP), X1.D+
unnamed: U$1.P$9 (RXD), U$3.P$1 (IN), U$5.1 (TXD)
unnamed: U$1.P$8 (TXD), U$3.P$2 (OUT), U$5.5 (RXD)
unnamed: R1.2, TX.C
unnamed: R2.2, RX.C
unnamed: R1.1, U$5.23 (TXLED)
unnamed: R2.1, U$5.22 (RXLED)
VBAT: D2.1 (C), U$1.P$7 (VBAT), U$2.P$1 (+)

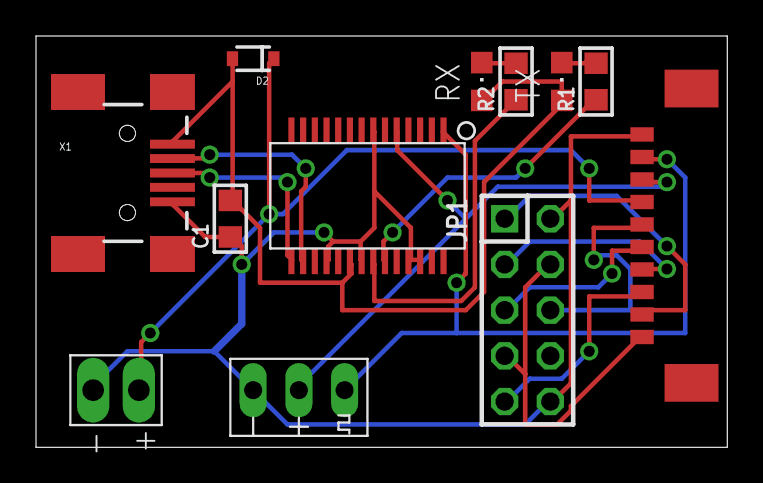
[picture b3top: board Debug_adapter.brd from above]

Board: 2 copper layers, 38.4 x 22.9 mm, 12 parts (0 on the bottom side), 17 nets.
